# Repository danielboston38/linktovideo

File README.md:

# Link to Video

A replacement for the RF modulator in the original Nintendo Entertainment System (NES-001). Drops into the stock RF module slot inside the shell and provides composite video and USB-C power in place of a part that fails by design.

> [!CAUTION]
> **Safety advisory for boards built before 2026-09-08.**
> On every board fabricated so far, the USB-C VBUS input reaches F1 through 9.06 mm of
> 0.2 mm-wide trace. That trace fails at a current well below F1's guaranteed trip
> current. If a fault occurs downstream, **F1 cannot protect the input trace on the
> board**.
> The defect has no effect on normal operation (48 °C, 17 mV drop). It is a
> fault-tolerance defect, not a wear-out defect: a board that works now will keep working.
> Commit [`247334c`](../../commit/247334c) corrects the layout. Reworking an affected
> board takes about 15 minutes.
>
> **→ Read the full advisory: [docs/SAFETY-ADVISORY-2026-09-vbus-trace-ampacity.md](docs/SAFETY-ADVISORY-2026-09-vbus-trace-ampacity.md)**

> **Renamed.** The first revision of this project was called **Kirby's New Dream**.
> From v2 on, it is **Link to Video**. Anything carrying the old name is the same
> project: the v1 board silkscreen, the 2026-07-16 PCBWay fab package, and older commits.
> The GitHub repository has been renamed too, and the old `kirbysnewdream` URL still
> redirects to it.

## Why this board exists

The NES-001's RF modulator already carries composite video, so this isn't about
adding an output the console lacks. It's about replacing a part that reliably
destroys itself.

Nintendo packed the modulator's regulator and RF stages into a sealed can with no
ventilation. It cooks its own electrolytics, they leak, and the electrolyte eats
the traces underneath. Across three NES-001 units on the author's bench, **all
three** had modulator failures from exactly this — including a Mitsumi unit that
looked pristine externally and had every capacitor leaking inside.

So the modulator is a consumable on a forty-year-old console, and the usual
options are to recap a corroded board or to fit an aftermarket board. This is the
second option, with the power input modernised to USB-C while the slot is open.

## Disclosure

This project's schematic design, debugging, and documentation were developed with the assistance of AI (Claude, by Anthropic). All hardware was hand-assembled, tested, and validated by the author. Use, review, and verify independently before building.

## Status

🟡 First prototype assembled and power-tested successfully (5V confirmed clean on rail, no protection trips). Video output path **does not work on v1 hardware** — traced to a schematic defect in which Q1's emitter node was shorted to the +5V rail (see Known Issues). Fixed in source; v1 boards need a rework.

<!-- Swap the line above for something like this once video's confirmed:
🟢 Fully validated — power and composite video both confirmed working on hardware.
-->

## Features

- USB-C power input (power only, no data lines)
- Composite video output
- Active overcurrent protection: TPS2553 eFuse with a ~1.18 A resistor-programmed limit, soft-start and thermal shutdown, and a polyfuse as backup
- Fits inside the original NES shell at the stock RF module location
- Bring-up test points for video, ground, +5 V and audio, labeled on the silkscreen
- Header that feeds an external 8-pin mini-DIN RGB connector (NESRGB)
- All resistor and capacitor values printed on the silkscreen (v1 had four identical, unlabeled axial footprints holding four different values, which led to three wrong-resistor build errors)
- 2-layer PCB, designed in KiCad

## Power path

```
USB-C  ──  F1 polyfuse  ──  U1 TPS2553 eFuse  ──  +5V rail  ──  J4.3 → NES
  VBUS      2.0A hold        ~1.18A limit          C1 100µF
            3.8A trip        soft-start            D1 TVS
            (backup)         thermal shutdown
```

F1 doesn't trip until 3.8 A. The console only draws about 0.5–0.7 A, so F1 alone
protects almost nothing. U1 gives the real protection. F1 is a backup in case the
eFuse fails short.

R6 on U1's ILIM pin sets the current limit. The relationship is
**inverse**: a larger resistor gives a *lower* limit.

| R6 | Limit (typ) |
|---|---|
| 15 kΩ | 1700 mA |
| 20 kΩ | 1295 mA |
| **22 kΩ (fitted)** | **~1180 mA** |
| 49.9 kΩ | 520 mA |
| 210 kΩ | 130 mA |

Approximately, I_OS(A) ≈ 25.9 / R6(kΩ). This is valid across TI's recommended range of
15 kΩ–232 kΩ.

U1's EN (pin 3) is active-high and tied to U1's own input, so the switch is always on.
FAULT (pin 4) is open-drain and left unconnected, because an indicator would not be visible
inside a closed NES shell. If you want a fault LED, FAULT can sink 25 mA directly.

**Useful side effect: a reversed D1 is survivable.** D1 is a unidirectional TVS, so
installing it backwards puts a forward-biased diode directly across the 5 V rail.
Before the board had U1, that was almost a short circuit, and the only protection
was the polyfuse, which takes seconds to react. Now the eFuse limits the current to
~1.18 A and then shuts down thermally, so the mistake does not destroy any parts.

## Test points (v2)

The board has four through-hole test points (2.0 mm pad, 1.0 mm drill) for bring-up.
Each takes a 0.64 mm square header pin, so you can solder in pins and attach scope
grabbers to them.

The silkscreen shows only the signal name (`VIDEO`, `GND`, `+5V`, `AUDIO`), so you
can read the board without this table. The reference designators are on F.Fab, for
the fab drawings.

The first pass of v2 had this backwards: the signal names were on F.Fab, which never
reaches the physical board, so the silkscreen showed only `TP1`–`TP4`.

| TP  | Net          | Location (mm) | Notes |
|-----|--------------|---------------|-------|
| TP1 | `/VIDEO_OUT` | 62.0, 60.0    | Jack-side video, after C2 and the 75 Ω series resistor R5. This is what the TV sees. A high-impedance probe reads roughly double the terminated amplitude. |
| TP2 | `GND`        | 58.5, 60.0    | Connects directly to the B.Cu ground pour. |
| TP3 | `/5V`        | 52.0, 43.1    | On the protected 5 V trunk, downstream of F1 and the TPS2553. |
| TP4 | `/AUDIO_OUT` | 65.9, 28.35   | Audio pass-through between J4 pin 2 and J2. |

TP2 is only there for convenience. The whole back layer is ground pour, so any B.Cu feature
works for a ground clip.

To probe the buffer itself rather than its output, probe Q1's emitter leg directly.
`Net-(Q1-E)` has no test point.

## RGB output (v2)

This board can feed the RGB connector for the [NESRGB](https://etim.net.au/nesrgb/)
board, which uses the 8-pin mini-DIN pinout of the Micomsoft XRGB-mini Framemeister.

The connector itself is **not** on this board. It comes with the NESRGB kit as a
panel-mount jack that is epoxied into a 12 mm hole in the shell. R/G/B go directly
from the NESRGB to that jack, and **J5** on this board supplies the other three pins:

| J5 pin | Net          | mini-DIN pin | |
|--------|--------------|--------------|---|
| 1 | `/RGB_VIDEO` | 3 | Composite video / sync, 75 Ω terminated |
| 2 | `GND`        | 4 | |
| 3 | `/5V`        | 5 | Downstream of the TPS2553, so it is current-limited |

Mini-DIN pins 1 and 2 are unconnected. Pins 6, 7 and 8 are Blue, Green and Red from
the NESRGB. The pinout carries no audio, so audio stays on the RCA jack. That was a
deliberate choice by Tim Worthington, to keep video noise out of the audio.

**Why R7 exists.** The output of the video buffer (`/VIDEO_BUF`, Q1's emitter
through C2) now feeds two outputs, and each needs its own 75 Ω source termination:
R5 for the RCA jack, R7 for the mini-DIN. A single shared resistor would put two
75 Ω loads in parallel whenever both cables were plugged in, halving the amplitude.

**One output at a time.** Composite and RGB are alternatives, and the design doesn't
target using both at once. The connected cable sees a correct 75 Ω source, and the unused
branch is an unloaded stub.

If both cables are plugged in, R7 still gives each output a correctly
terminated 75 Ω source, and the amplitude doesn't halve. The limit then becomes Q1's
drive, which is why **R1 is 220 Ω from v2**, down from the original 330 Ω.

In an ngspice simulation with 2 Vpp at the tap and both outputs terminated, the
follower clips the positive (white) peaks by 33 % at 330 Ω and by 11 % at 220 Ω.
With one output loaded (the supported mode), 220 Ω is clean and symmetric
(+0.439 / −0.447 V at the jack). These are simulated numbers, not bench
measurements, and driving both outputs is still unsupported.

## Hardware

- Designed in KiCad (schematic + PCB source included in this repo)
- Fabricated by PCBWay
- See [BOM.csv](./BOM.csv) for the full parts list

### Sponsored by PCBWay

The most recent fabrication run of this board — the 2026-08-26 package, ordered
**2026-08-27** — was
**sponsored by [PCBWay](https://www.pcbway.com/)**, who covered the manufacturing
of the boards this project is built and tested on. Thank you — having the fab
covered is what let this revision get made, populated and put on the bench rather
than staying a set of gerbers.

Those boards predate [`247334c`](../../commit/247334c), so like every board
fabricated so far they carry the `/raw_5v` trace-ampacity defect described in the
caution at the top of this file — see
[the safety advisory](docs/SAFETY-ADVISORY-2026-09-vbus-trace-ampacity.md).

PCBWay have been good to work with on the practical side too: the 2-layer,
1.6 mm FR4 board here is an unremarkable order for them, the gate-generated fab
package uploaded without any back-and-forth over the drill or layer files, and
they will run the four SMD lines (C3, R6, U1, USB-C1) as single-sided SMT while
leaving the through-hole parts to the bench — including sourcing the TPS2553
from LCSC, which DigiKey and Mouser have on a 112-day lead. See
[docs/pcbway-smd-assembly.md](./docs/pcbway-smd-assembly.md) for that workflow.

The project is also published on PCBWay's community site, with the same design
files and documentation as this repository:

**→ [Link to Video on PCBWay Community](https://www.pcbway.com/project/shareproject/Link_to_video_7f1f9279.html)**

The sponsorship covered fabrication only, and carries no editorial influence over
this documentation. The design remains [CERN-OHL-S v2](./LICENSE.txt) and
OSHWA-certified, free for anyone to study, modify, build and have made wherever
they like. The PCBWay-hosted copy is published under GPL v3 because their form
does not offer CERN-OHL-S — see [License](#license).

## Build Notes / Known Issues (v1)

- **Q1 emitter node shorted to +5 V (breaks video).** The rail clamps Q1's emitter,
  so C2 couples +5 V, not video, into R5/J3.

  The exact wiring differs between revisions. In the pre-v1.1 source in this
  repository, R1 had *both* ends on `/5V`. On the boards fabricated from the
  2026-07-16 gerbers, R1 pad 1 is on `/5V` and pad 2 is on a separate net with only C1.

  Root cause: an edit on 2026-07-04 deleted an R2 (110 Ω) from the schematic, and
  KiCad merged the two leftover collinear wire stubs into a single wire that tied the
  emitter node to `/5V`. The source is fixed as of v1.1. To rework an existing board,
  see [Q1 emitter rework (v1 boards)](#q1-emitter-rework-v1-boards).
- The mounting holes of the RCA jack are slightly asymmetric. This is cosmetic and
  doesn't affect the fit in the NES shell.
- The v1 silkscreen has no component values and no E/C/B markers for Q1.
  **v2 adds the values.** R1/R3/R4/R5/R7 share one footprint across four values, and
  on v1 that led to three wrong-resistor errors in R1: a 5.1 kΩ and an 820 Ω both
  went in before the correct value. Q1 pin markers are still missing.
- **VBUS input trace is undersized for its own fuse (all fabbed boards).** `/raw_5v`
  reaches F1 through 9.06 mm of 0.2 mm trace. At 2.22 A the trace heats above the glass
  transition of FR4, and at 2.83 A it chars. F1 (RHEF200) is guaranteed to hold up to
  2.0 A but only guaranteed to trip above 3.8 A, so in the 2.2–3.8 A window the trace
  can be destroyed before the fuse trips.

  Root cause: a gap in the netclass patterns. `/5V*`, `GND*` and `VBUS` were assigned
  the `Power` class (0.8 mm), but none of them matched the actual net name `/raw_5v`,
  so it got the `Default` class (0.2 mm). DRC can't catch this, because it enforces
  the board's `min_track_width` (0.2 mm), not the netclass width. Commit `247334c`
  fixes the pattern and reroutes the trace at 0.8 mm.
  **Existing boards need a rework.** See
  [the safety advisory](docs/SAFETY-ADVISORY-2026-09-vbus-trace-ampacity.md).

- **D1 does not protect U1.** The installed TVS is a Littelfuse 1.5KE6.8A: stand-off
  5.80 V, breakdown 6.45–7.14 V at 10 mA, clamping 10.5 V at 144.8 A. The TPS2553's
  absolute maximum on IN and OUT is 7 V, and at 7 V the TVS has only started
  to conduct. In a real surge, it lets the rail reach 10.5 V. D1 protects the console
  downstream, but not U1.

  Moving D1 wouldn't help, since both U1 pins share the same 7 V rating, and no
  avalanche TVS both clamps below 7 V and stands off USB-C's 5.5 V worst case. The
  real fix is a switch with a built-in overvoltage cutoff. That's a v3 change. v2
  ships with this gap.
- D1's symbol (`Diode:1.5KExxA`) labels its pins A1/A2 and shows no cathode, because
  KiCad uses the same pin names for the unidirectional and bidirectional variants of
  this part. Only the footprint's silkscreen band shows the polarity. The band is at
  the pad-1 (+5 V) end, which is correct. Use the band when you assemble by hand.

### Q1 emitter rework (v1 boards)

This applies to boards fabricated from the 2026-07-16 gerbers, whose IPC netlist
reads:

- `/5V = J4.3, F1.1, R1.1, Q1.1, C2.1, D1.1`
- `Net-(C1-Pad1) = R1.2, C1.1`

That revision has two defects:

- The rail clamps Q1's emitter.
- C1 only reaches the rail through R1, so the bulk capacitor isn't decoupling the
  rail.

This procedure fixes both at once.

> [!CAUTION]
> **Do not power the board with Q1 installed until the cut is done.** This short destroys transistors.
> With the emitter clamped at +5 V and the base at the NES video level, the B-E
> junction is forward-biased by 3–4 V. Q1 saturates, with its collector connected directly to
> ground, and nothing limits the current: Q1 is a 150 mA part, and F1 won't trip until
> 3.8 A. Every power-up in that state can destroy another transistor. The first
> transistor probably failed this way.

**Confirm the diagnosis before you cut.**

1. Disconnect the power.
2. Make sure the capacitors are discharged.
3. Put one meter lead on +5 V, at J4 pin 3 or at D1's K-marked lead.
4. Take the two measurements in the table. A defective board and a correct board
   give opposite results:

| Measurement | Defective board | Correctly wired |
|---|---|---|
| Q1 emitter → +5 V | **~0 Ω** | ~330 Ω (R1) |
| C1 **+** terminal → +5 V | **~330 Ω** (stranded behind R1) | ~0 Ω |

After the rework, the two readings change places.

To identify Q1's legs without relying on the TO-92 orientation, measure each leg:

- 0 Ω to GND: collector
- Continuity to J4 pin 1: base
- The remaining leg: emitter

Two tests look useful but aren't:

- **Emitter → J3 tip.** C2 blocks DC, so this reads open on every board.
- **C1 + → Q1 emitter.** This reads ~330 Ω on good and bad boards alike, because R1
  sits between these two points in both wirings.

With power on, the quickest check is the DC voltage at Q1's emitter: about 1.5–3 V
on a correct board, exactly the rail voltage on a shorted one.

**R1's left pad is a star point.** Three connections meet there:

- F1 (the source)
- The D1 + J4.3 branch (the load)
- Q1's emitter

The two incoming rail traces are *collinear*, so one cut severs both. That's why the
rework needs **two** jumpers, not one.

1. **Cut** the 0.8 mm trace that runs from R1's left pad toward the **upper
   left**, about 5–8 mm from the pad.

   Leave the trace coming in from the upper right alone. That one is Q1's emitter.

   Cut below the level of D1's cathode. Above that point, only one of the two
   overlapping traces is present, and you need to cut both.

2. **Install two jumpers.** Pull R1 first. Its right pad is much easier to solder
   when it's empty.

   The cut leaves three islands. Join all three into one rail:

   | Island | Pads |
   |---|---|
   | A | C1's **+** pad, R1's **right** pad |
   | B | F1 pad 1 (left pad, trace toward D1 — not the USB-C side) |
   | C | D1's cathode (K), J4 pin 3 |

   Any two wires that join all three islands will work. For example, with one wire
   per pad:
   - **C1+ → F1 pad 1** (~14 mm)
   - **R1's right pad → D1 cathode** (~25 mm)

3. **Install R1 = 300–330 Ω.** Double-check the part before it goes in. R1, R3, R4,
   R5 (and R7 on v2) share the same `R_Axial_DIN0207` footprint across four different
   values, and the v1 silkscreen shows none of them.

   At least one board got a 5.1 kΩ resistor from the R3/R4 parts in the R1 position.
   That gives ~0.6 mA of standing current instead of ~9 mA. The board looks plausible
   but produces no usable video.

4. **Check that R5 (75 Ω) is fitted.** Measure across its pads. You should see
   ~75 Ω. R5 has no parallel path in the circuit (C2 blocks DC on one side and the
   jack is open on the other), so this is also a check of the meter.

5. **Install the transistor last.** If you power up before the cut is complete, Q1
   saturates and current flows from the rail directly to ground with no limit. See the caution above.

Before you power up, check with a meter:

- R1 left pad to D1 cathode: **open**
- R1 left pad to F1 pad 1: **~330 Ω**, through R1
- R1 left pad to Q1's emitter and to C2 pin 1: continuity
- D1 cathode to J4 pin 3 *and* to F1 pad 1: **~0 Ω**

With power on, Q1's emitter should sit at about 1.5–3 V. If it reads 5 V, the cut
didn't separate the traces.

## Video input biasing

Q1's base is DC-coupled directly to the NES video line, with no bias network. That's
deliberate, and it took a long bench session to work out why it works.

**The NES mainboard supplies a 1 kΩ pulldown on its video output pin.** It measures
0.999 kΩ in circuit, the same with the meter leads in either direction, so it's a real
resistor and not a semiconductor junction. Q1's base sources about 46 µA, and that
1 kΩ absorbs it with about 46 mV. The base can't float up, and Q1 can't cut off.

That's also why Nintendo's original modulator has no base pulldown. It's consistent
with the load Nintendo put on that pin, too: a 330 Ω series resistor into a
5.6 kΩ / 330 Ω divider, roughly 500 Ω in total. The NES is designed to drive a few
hundred ohms.

**So this board has no base pulldown and no input coupling capacitor.** If you
adapt this design for something other than an NES-001, measure that pin to ground
first, and if it reads open, add a pulldown (~47 kΩ).

**R2 (330 Ω) is not a bias resistor.** It sits in series between J4 pin 1 and Q1's
base, in the same position as Nintendo's own 330 Ω. Against Q1's ~21 kΩ base input
impedance it has almost no effect on the signal. Its job is to limit fault current
into the base-emitter junction, which is only rated for 5 V in reverse.

## Design checks

Beyond ERC and DRC, this project runs three more checks. The first two catch faults
this board actually shipped with. The third closes the gap between checking a board
and fabricating it.

### `tools/check_nets.py`

```
python3 tools/check_nets.py
```

The script exports the schematic netlist, reads the pad nets from the PCB, checks
that the two agree, and then asserts a set of invariants.

The most important invariant is that **Q1's emitter is not on any power net**.
That was the v1 fault: the emitter follower's output was tied to +5 V along with
J4.3, D1.1 and F1.1, so Q1 saturated into a grounded collector with nothing limiting
the current. Every power-up destroyed a transistor.

**ERC and DRC both passed on that board with no errors.** Neither can tell that a
net is *wrong*, only that it's internally consistent. That's why this script exists.

Run it before you generate a fab package. Gerbers carry no net information, so once
they're generated the mistake is invisible.

### `nes_power_video.kicad_dru`

Custom DRC rules for the geometric half of the problem:

- More clearance between the supply rails and the emitter and base nodes
- More clearance between the two USB-C configuration channels

These catch the same class of mistake when it shows up as adjacent copper in the
layout. They can't catch a wrong net assignment, because DRC knows nothing about
design intent. That's what the script above is for.

### `prefab-gate`

```
export KICAD_CLI=/Applications/KiCad/KiCad.app/Contents/MacOS/kicad-cli
prefab_gate package nes_power_video.kicad_pcb --out pcbway_production
```

**prefab-gate is now in its own repository:
[danielboston38/prefab-gate](https://github.com/danielboston38/prefab-gate).**
It's a general-purpose KiCad tool with its own MIT license and users beyond this
project, so it moved out of this hardware repo.

You can install it any of these ways:

- As a KiCad plugin, through the Plugin and Content Manager
- As a Claude Code plugin: `/plugin marketplace add danielboston38/prefab-gate`
- By cloning the repository and running `scripts/prefab_gate.py` directly

The gate refuses to write a fab package unless the board passes both DRC with zone
refill *and* schematic parity. It hashes the board and the schematic after the
refill and checks them again just before publishing, so the package always
describes the board the gate actually verified. `manifest.json` records the result
along with every finding, including the cosmetic findings the gate waived.

To get the verdict without writing files, run `check` instead of `package`.

`pcbway_production/` isn't tracked in git, since the packages can be regenerated
from the board. The first two fab packages are still in the git history, at the
2026-07-07 and 2026-07-16 commits. The 2026-08-26 package for the sponsored run was
never committed, but its copper and outline gerbers have been checked byte-identical
to the board at [`f672f8d`](../../commit/f672f8d), and all 49 drill hits match.

When you order, generate a fresh fab package rather than reusing an old directory,
so the gate re-verifies the exact board you're paying for.

## Assembly

<!-- Add step-by-step or reference photos here once you've got a documented build process -->

See BOM.csv for the exact part values and footprints. Every component's sourcing
data is in two places, and the two agree:

- The `Manufacturer`, `MPN`, `LCSC`, `Supplier Link` and `Datasheet` fields on the
  schematic symbol
- The matching columns in `BOM.csv`

Generic passives deliberately have no manufacturer part number. They carry a `Spec`
field instead (tolerance, rating, package), and any part that meets it is correct. To
get the fields directly from the schematic:

```
kicad-cli sch export bom --group-by '' \
    --fields 'Reference,Value,Manufacturer,MPN,LCSC,Datasheet,Supplier Link,Spec' \
    -o bom.csv nes_power_video.kicad_sch
```

The `Mount` column in `BOM.csv` marks each line `SMD` or `THT`, taken from the
footprint attributes on the board.

### Having PCBWay fit the SMD parts

Only four parts need reflow — C3, R6, U1 and USB-C1 — and all four are on the top
side. PCBWay can do those as single-sided SMT while you hand-solder the 15
through-hole parts. You don't have to solder the two most difficult joints on the
board (the SOT-23-6 and the Type-C receptacle), and you don't pay for full assembly.

`tools/pcbway_assembly.py` builds the SMD-only upload pair from a gate-generated fab
package. It takes the SMD/THT split from the board, not from a manual list:

```
python3 tools/pcbway_assembly.py nes_power_video.kicad_pcb pcbway_production/<timestamp>
```

Two things to know before you order:

- **U1 is out of stock at both DigiKey and Mouser** (112-day factory lead). LCSC has
  44,000, so tell PCBWay to source U1 from LCSC.
- **USB-C1 is Hybrid, not SMD.** Its four shell stakes are through-hole pads on the
  paste layer, and they must reflow pin-in-paste with everything else. Don't leave
  them dry.

As of v2, all four SMD lines (C3, R6, U1, USB-C1) are LCSC parts, so PCBWay can source
the whole assembly BOM from LCSC. For the full workflow, including what to upload and
what not to, see **[docs/pcbway-smd-assembly.md](./docs/pcbway-smd-assembly.md)**.

Key notes:
- D1 (zener/TVS): put the cathode (banded end) toward the VBUS/+5V side. From v2, the
  silkscreen shows the actual part, `1.5KE6.8A`. Earlier boards show KiCad's generic
  symbol name, `1.5KExxA`, which isn't an orderable part.
- Q1 (**2SA733**, PNP): with the flat side facing you and the leads down, the pins are
  Emitter-Collector-Base, left to right.
  This replaces the 2SA1015/KSA1015, **both of which are end of life** (checked 2026-08-29): MCC's
  `2SA1015-GR-AP` is stocked at Mouser but flagged End of Life, and every onsemi `KSA1015` reads
  Obsolete on DigiKey, available only through Rochester Electronics' last-time-buy channel. The
  2SA733 is in current production, shares the E-C-B pin order exactly so it drops straight in, and is
  a better part for a video buffer: f_T 190 MHz typ against the 2SA1015's 80 MHz, C_ob 2–3 pF, P_C
  750 mW, with the same V_CEO −50 V / I_C −150 mA / V_EBO −5 V — so R2 still guards the base-emitter
  junction exactly as before. Buy the UTC `2SA733L-P-T92-B` from LCSC (**C5310429**, ~$0.035).
  Rank P is hFE 200–400, which matches the ~46 µA base current measured on the bench, so the bias
  point does not move. DigiKey's Renesas 2SA733 is Rochester stock at $1.90 — same trap, different part.
- **Why not a 2N3906 or BC557?** Not for the reason you might assume. Electrically the 2N3906 is
  perfectly happy here — V_CEO −40 V, I_C −200 mA, f_T 250 MHz, V_EBO −5 V, hFE 100–300 at 10 mA,
  every figure with huge margin against a 5 V rail at ~9.3 mA. The problem is the middle pin. Per
  UTC's ordering tables, the 2N3906 is **E-B-C** and the 2SA733 is **E-C-B**: the 3906 puts *base* in
  the centre where this board wants *collector*. Turning the part around gives C-B-E — base is still
  in the middle, so no orientation fixes it and you would have to cross two leads. On a v3 layout the
  pin order is free and the 2N3906 becomes a fine choice; on this board it is not. Pin order is a
  manufacturer's choice rather than a standard, so check the datasheet of the exact brand you buy.
- R1 (220 Ω): Q1's emitter load. One end goes to +5 V and the other to the Q1 emitter /
  C2 node; both ends on +5 V is wrong. v2 dropped R1 from 300 Ω to 220 Ω for more
  drive current. Assuming ~1.3 V at the base, 300–330 Ω gives only ~6.2 mA at peak
  white, and the 150 Ω load needs ~6.7 mA. If you measure something other than ~1.3 V
  DC at J4 pin 1, recalculate R1.
- R2 (330 Ω): series resistor in the video input line, between J4 pin 1 and Q1's base. See [Video input biasing](#video-input-biasing).
- **Trim all through-hole leads flush.** The board sits in the RF module slot with
  shielding directly underneath, and long leads on the bottom side will short to the
  can. On the prototype, this caused an intermittent supply trip that only happened
  when the board moved.
- C2 (470 µF): not 100 µF. Into the 150 Ω load, 100 µF gives τ=15 ms against a
  16.7 ms field period, so the picture tilts from top to bottom. 470 µF gives τ=70 ms.
- F1 (polyfuse): it's fine for it to sit slightly off the PCB. That's normal for
  radial-lead parts, not a defect.

  **KiCad has no footprint for the Littelfuse RHEF series.** F1 borrows
  `Fuse:Fuse_Bourns_MF-RG300`: pads 5.24 mm center-to-center, with 1.01 mm drills. The
  RHEF200's 0.51 mm leads at 5.05 ±0.75 mm spacing fit easily. But the Bourns part is
  rated 3.0 A/5.1 A and the silkscreen outline shows *its* body, so treat the outline
  as a rough guide, not a clearance boundary. A proper RHEF200 footprint moves pad 2 by
  ~1.2 mm and needs a reroute, so that's a v3 change rather than a patch.

  **F1 stays a Littelfuse RHEF200 and is deliberately not an LCSC part.** It's
  through-hole, so it isn't on the SMD assembly BOM that PCBWay sources. Also, the
  LCSC alternatives are worse in the important specifications:
  - Jinrui JK30-200 (C369104): I_max drops to 40 A, and the part is 15.2 mm tall.
  - JKSEMI JK16-200T (C5183874): LCSC lists it as through-hole, but its datasheet is
    titled *"JK16 Series Surface Mount PTC Devices"* and shows no land pattern, so its
    package is unconfirmed.

  If you need to reorder F1, get it from DigiKey or Mouser along with the Switchcraft
  RCA jacks, which LCSC can't supply either.
- USB-C1: GCT USB4125-GF-A-0190, SMD receptacle. Power-only, 6P, no data lines,
  48 V / 3 A, 20,000 mating cycles.

  **As of v2, this part replaces the GCT USB4970-00-A**, which LCSC doesn't stock (a
  search for that MPN turns up nothing). The USB4125 is a different GCT line that LCSC
  *does* stock (C5246813). The board already used its land pattern, so this is a
  sourcing change only, not a layout change.

  The footprint is `Connector_USB:USB_C_Receptacle_GCT_USB4125-xx-x-0190`. Its copper,
  silk, fab, courtyard and drills are byte-identical to the plain `USB4125-xx-x`
  variant the board used before. Only the name, the descr field and the 3D model
  differ.

  Use the **-0190** variant. Its 1.90 mm shell stake goes 0.30 mm through this 1.6 mm
  board and gives a fillet on the bottom side. The 1.00 mm stake (plain
  `USB4125-GF-A`, C3151650) doesn't go through the board. LCSC stocks fewer of these than
  of the generic Chinese 6P parts, so order spares.
- U1 (TPS2553, SOT-23-6): pin 1 (marked by the dot on the package) is IN. The pins run
  IN, GND, EN down one side and OUT, ILIM, FAULT up the other. Order the plain
  TPS2553DBVR. The `-1` suffix is the latch-off variant, which needs a power cycle
  after every trip. The plain part retries automatically.
- C3 (100 nF, 0805): TI wants C3 as close to U1 pin 1 as the layout allows. It sits
  immediately to the left of U1.
- R6 (22k, 0805): sets the current limit. Check the table in
  [Power path](#power-path) before you change it.

## Certification

This project is **OSHWA-certified open source hardware**, UID **[US002842](https://certification.oshwa.org/us002842.html)**.

The certification confirms that the design files, schematics, PCB layout, bill of
materials and documentation in this repository:

- Are published under an OSI/FSF-approved open license
- Are complete enough for someone else to study, modify, manufacture and distribute
  the hardware

See the [OSHWA certification directory entry](https://certification.oshwa.org/us002842.html)
for the registered details.

The certification mark above,
[`certification-mark-US002842-stacked.svg`](./certification-mark-US002842-stacked.svg),
was issued by OSHWA for this UID. It applies only to this design and doesn't transfer
to derivatives. Each derivative needs its own certification.

## License

Licensed under [CERN-OHL-S v2](./LICENSE.txt) (strongly reciprocal open hardware license). See [LICENSE](./LICENSE.txt).

**The PCBWay community copy is GPL v3.** PCBWay's project form doesn't offer
CERN-OHL-S, so the copy
[on their community site](https://www.pcbway.com/project/shareproject/Link_to_video_7f1f9279.html)
is licensed GPL v3. Same design, same files, two license grants: use whichever one
you received the design under. Both licenses are copyleft and both are on the
approved list, so the certification holds either way.

The practical difference is the physical board. CERN-OHL-S covers the *making* of
hardware: if someone builds and sells a board, the complete source has to go with
it. GPL v3's copyleft starts when someone distributes the design files, so it
doesn't apply to a board fabricated from them. Both licenses keep the design files
reciprocal. Only CERN-OHL-S does the same for manufactured hardware.

## Photos

<!-- Add build photos here -->

## Acknowledgments

- **[PCBWay](https://www.pcbway.com/)** — for sponsoring the fabrication of the
  latest revision of this board, and for hosting the project on their community
  site: [Link to Video](https://www.pcbway.com/project/shareproject/Link_to_video_7f1f9279.html).
- **Tim Worthington** — for the [NESRGB](https://etim.net.au/nesrgb/), whose
  8-pin mini-DIN pinout J5 on this board feeds.
- **OSHWA** — for the open hardware certification programme
  ([US002842](https://certification.oshwa.org/us002842.html)).

<!-- Optional: credit anyone who helped with debugging, Discord community, etc. -->

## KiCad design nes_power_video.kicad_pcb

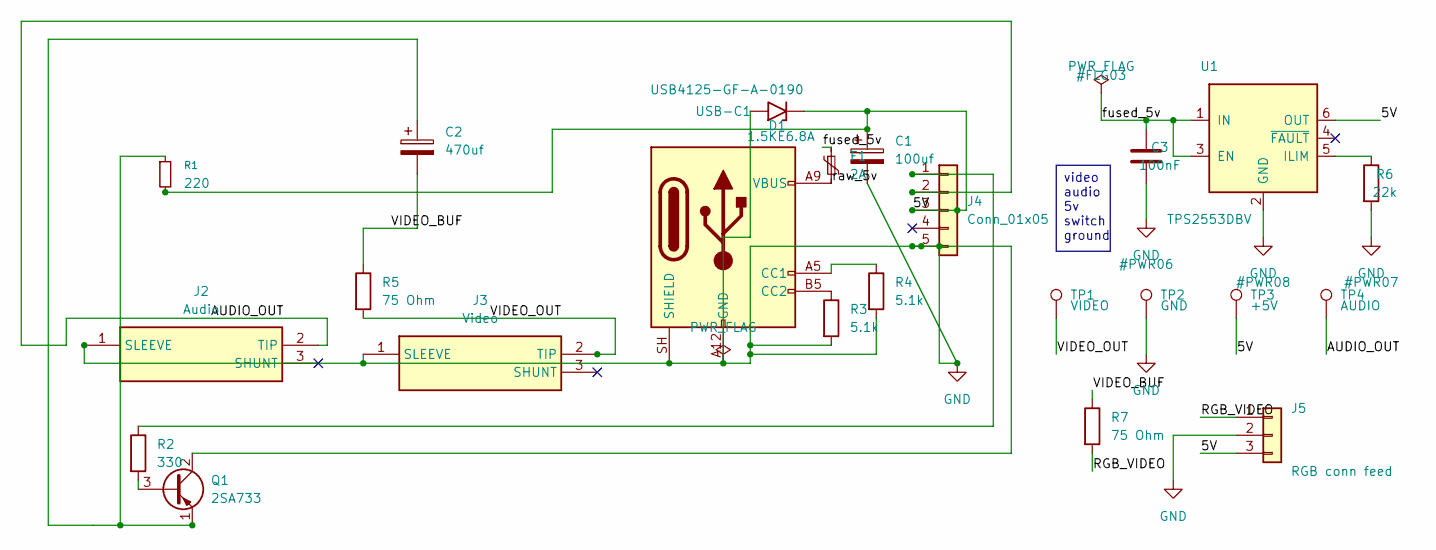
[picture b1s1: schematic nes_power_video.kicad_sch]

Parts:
C1: 100uf; CP_Radial_D10.0mm_P5.00mm
C2: 470uf; CP_Radial_D10.0mm_P5.00mm
C3: 100nF; C_0805_2012Metric_Pad1.18x1.45mm_HandSolder; MPN CC0805KRX7R9BB104; LCSC C49678
D1: 1.5KE6.8A; D_DO-201AE_P15.24mm_Horizontal; MPN 1.5KE6.8A; LCSC C294199
F1: 2A; Fuse_Bourns_MF-RG300; MPN RHEF200
J2: Audio; PJRAN1X1U03X; Mouser Part Number 502-PJRAN1X1U03X
J3: Video; PJRAN1X1U03X; Mouser Part Number 502-PJRAN1X1U03X
J4: Conn_01x05; PinHeader_1x05_P2.54mm_Vertical
J5: RGB conn feed; PinHeader_1x03_P2.54mm_Vertical
Q1: 2SA733; TO-92_Inline; MPN 2SA733L-P-T92-B; LCSC C5310429
R1: 220; R_Axial_DIN0207_L6.3mm_D2.5mm_P7.62mm_Horizontal
R2: 330; R_Axial_DIN0207_L6.3mm_D2.5mm_P7.62mm_Horizontal
R3, R4: 5.1k; R_Axial_DIN0207_L6.3mm_D2.5mm_P7.62mm_Horizontal
R5, R7: 75 Ohm; R_Axial_DIN0207_L6.3mm_D2.5mm_P7.62mm_Horizontal
R6: 22k; R_0805_2012Metric_Pad1.20x1.40mm_HandSolder; MPN 0805W8F2202T5E; LCSC C17560
TP1: VIDEO; TestPoint_THTPad_D2.0mm_Drill1.0mm
TP2: GND; TestPoint_THTPad_D2.0mm_Drill1.0mm
TP3: +5V; TestPoint_THTPad_D2.0mm_Drill1.0mm
TP4: AUDIO; TestPoint_THTPad_D2.0mm_Drill1.0mm
U1: TPS2553DBV; SOT-23-6_Handsoldering; MPN TPS2553DBVR; LCSC C55266
USB-C1: USB4125-GF-A-0190; USB_C_Receptacle_GCT_USB4125-xx-x-0190_6P_TopMnt_Horizontal; MPN USB4125-GF-A-0190; LCSC C5246813

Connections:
/5V: C1.1, D1.1 (A1), J4.3, J5.3, R1.2, TP3.1, U1.6 (OUT); also elsewhere on the board
/AUDIO_OUT: J2.2 (TIP), J4.2, TP4.1
/RGB_VIDEO: J5.1, R7.2
/VIDEO_BUF: C2.2, R5.1, R7.1
/VIDEO_OUT: J3.2 (TIP), R5.2, TP1.1
/fused_5v: C3.1, F1.1, U1.1 (IN), U1.3 (EN)
/raw_5v: F1.2, USB-C1.A9 (VBUS), USB-C1.B9 (VBUS)
GND: C1.2, C3.2, D1.2 (A2), J2.1 (SLEEVE), J3.1 (SLEEVE), J4.5, J5.2, Q1.2 (C), R3.2, R4.2, R6.2, TP2.1, U1.2 (GND), USB-C1.A12 (GND), USB-C1.B12 (GND), USB-C1.SH (SHIELD); also elsewhere on the board
unnamed: J4.1, R2.1
unnamed: Q1.3 (B), R2.2
unnamed: C2.1, Q1.1 (E), R1.1
unnamed: R6.1, U1.5 (ILIM)
unnamed: R4.1, USB-C1.A5 (CC1)
unnamed: R3.1, USB-C1.B5 (CC2)

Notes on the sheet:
video audio 5v switch ground

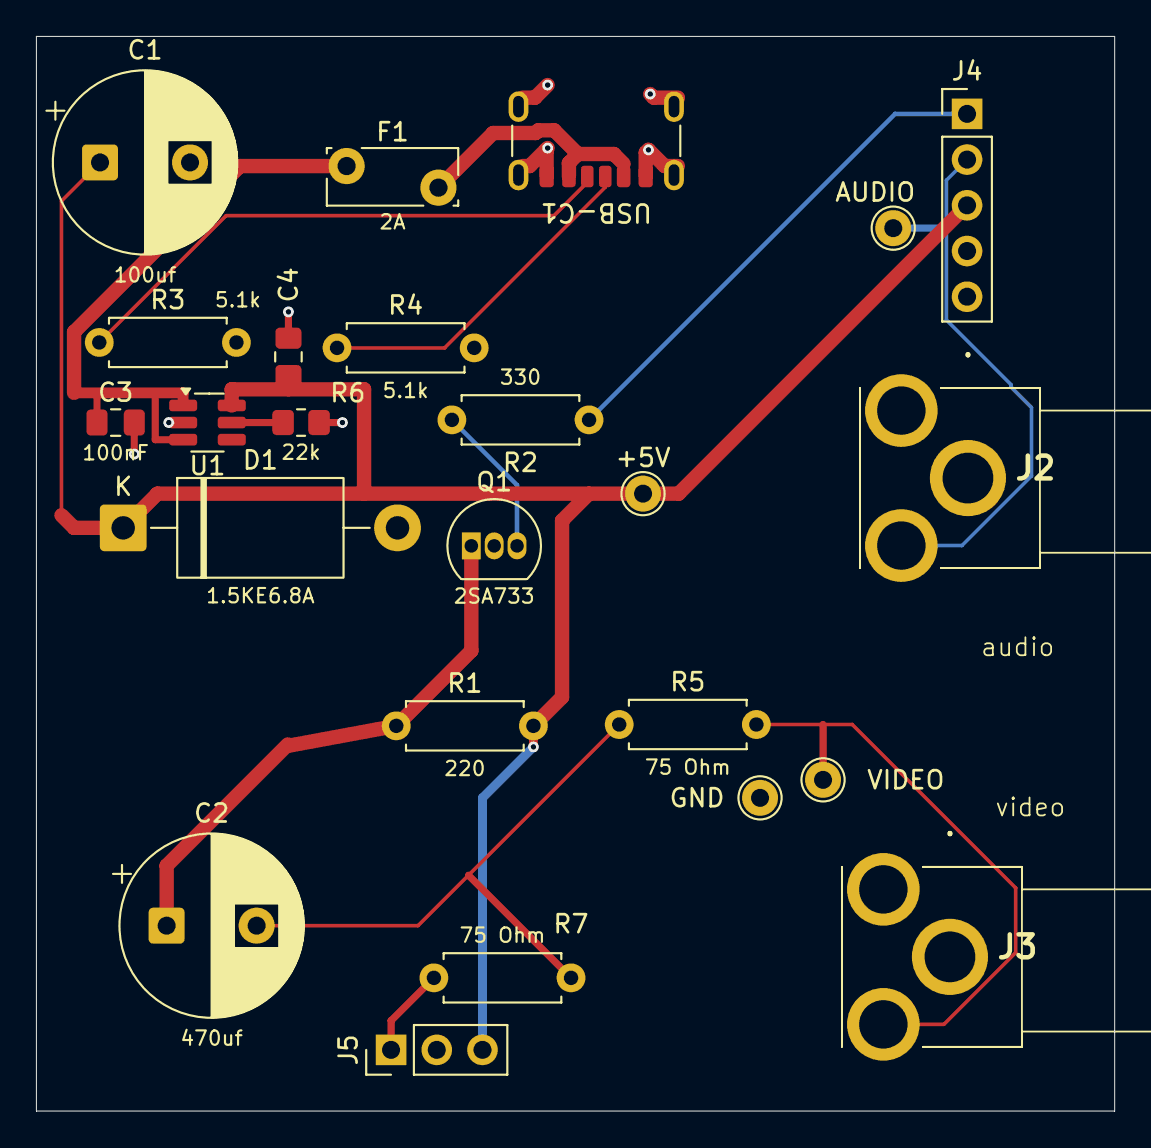
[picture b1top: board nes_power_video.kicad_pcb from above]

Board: 2 copper layers, 59.9 x 59.7 mm, 24 parts (0 on the bottom side), 14 nets.

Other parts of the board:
C4: 100nF; C_0805_2012Metric_Pad1.18x1.45mm_HandSolder

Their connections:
/5V: C4.1; also elsewhere on the board
GND: C4.2; also elsewhere on the board
